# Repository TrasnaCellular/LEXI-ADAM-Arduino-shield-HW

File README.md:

# Trasna LEXI-R10 Arduino schield board

The LEXI-ADAM UNO Shield is an open-source cellular expansion board for the Arduino UNO or Arduino UNO Q platforms. It uses the ultra-small LEXI-R10 series or ADAM-R11 series LTE Cat 1bis cellular modules. 

The Cellular module can be turned ON/OFF and Reset by the Arduino board. The shield has its own step down to deliver power to the cellular module; the stepdown too can be turned ON/OFF by an Arduino GPIO to minimise power consumption. The input voltage range of the shield is the same as Arduino's range. 

The Arduino UNO  communicates with the Cellular module via UART, and by default, this communication is without RTS/CTS handshake. The shield already supports RTS/CTS handshake by easy soldering jumpers. The proper modifications must be made also to the MCU firmware of Arduino (R7FA4M1AB3CFM for UNO, or STM32U585 for UNO Q) to support hardware handshake. To achieve communication with the Linux system of Arduino UNO Q, the Arduino Bridge feature should be used. For even higher higher communication rates with the Linux system the USB port of the UNO Q must be connected to the USB port of the shield.
 
The shield also features two breadboarding areas for experimenting with own circuits. They have 2.54mm and 1.27mm pitch and are provided with 3.3Volts, 1.8Volts and GND for powering the circuits that the user might implement.

All the hardware design source files, including Schematic, PCB board, gerbers, stack-up, can be downloaded from the present repository. Also the firmware examples running on Arduino UNO R4 WIFI and on Arduino UNO Q can be found here.

The user guide explaining the board can be downloaded from: [LEXI-ADAM_Arduino_UNO_Shield_UserGuide](https://drive.google.com/file/d/1tEk1xlIRyrKd_FjjbZdSfsDOfKxhqTxc/view).

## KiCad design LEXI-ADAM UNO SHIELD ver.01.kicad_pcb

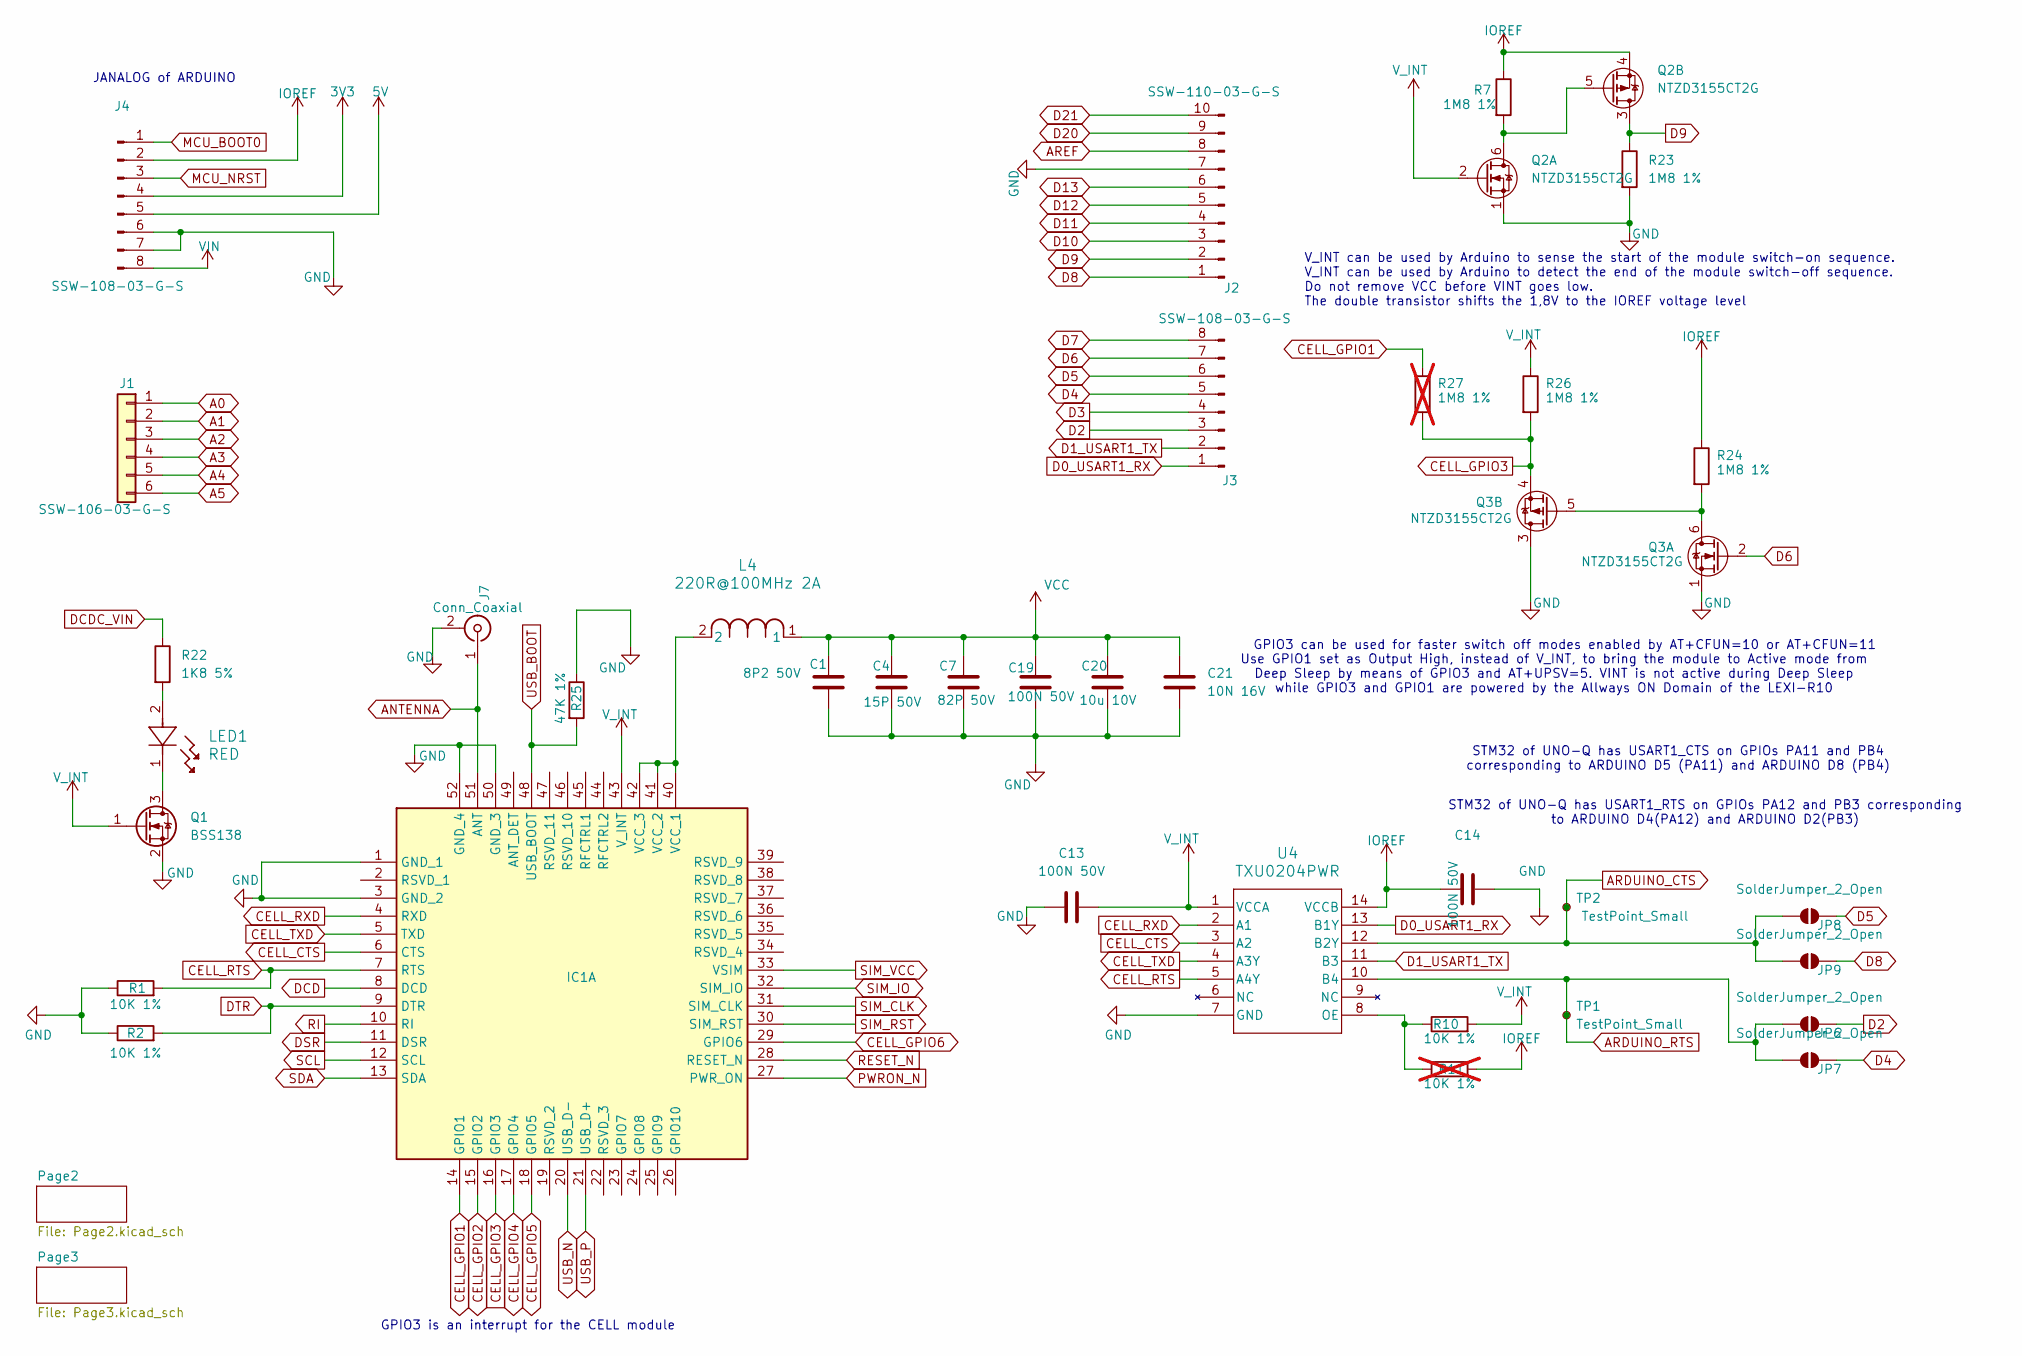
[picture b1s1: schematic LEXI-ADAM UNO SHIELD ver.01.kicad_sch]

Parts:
C1: 8P2 50V; C_0201_0603Metric; Manufacturer_Part_Number GRM0335C1H8R2DA01D
C4: 15P 50V; C_0201_0603Metric; Manufacturer_Part_Number GRM0335C1H150JA01D
C7: 82P 50V; C_0201_0603Metric; Manufacturer_Part_Number GRM0335C1H820JA01D
C13, C14, C19: 100N 50V; C_0402_1005Metric; Manufacturer_Part_Number GRM155R61H104KE14D
C20: 10u 10V; C_0402_1005Metric; Manufacturer_Part_Number GRM155R61A106ME11D
C21: 10N 16V; C_0201_0603Metric; Manufacturer_Part_Number GRM033R71C103KE14D
IC1: LEXI-R10011D; LEXIR10801D00B00; Manufacturer_Part_Number LEXI-R10011D
J1: SSW-106-03-G-S; Manufacturer_Part_Number SSW-106-03-G-S
J2: SSW-110-03-G-S; SSW-110-03-L-S; Manufacturer_Part_Number SSW-110-03-G-S
J3, J4: SSW-108-03-G-S; Manufacturer_Part_Number SSW-108-03-G-S
J7: Conn_Coaxial; U.FL_Hirose_U.FL-R-SMT-1_Vertical; Manufacturer_Part_Number CONUFL001-SMD-T
JP6, JP7, JP8, JP9: SolderJumper_2_Open; SolderJumper-2_P1.3mm_Open_RoundedPad1.0x1.5mm
L4: 220R@100MHz 2A; IND_BLM18_0603_MUR; Manufacturer_Part_Number BLM18EG221SN1D
LED1: RED; LED_LTST-C190_LTO; Manufacturer_Part_Number LTST-C190KRKT
Q1: BSS138; SOT-23; Manufacturer_Part_Number BSS138P,215
Q2, Q3: NTZD3155CT2G; SOT-563-6_1P3X1P7_ONS; Manufacturer_Part_Number NTZD3155CT2G
R1, R2, R10: 10K 1%; R_0402_1005Metric; Manufacturer_Part_Number RK73H1ETTP1002F
R7, R23, R24, R26: 1M8 1%; R_0402_1005Metric; Manufacturer_Part_Number CRCW04021M80FKEDC
R11: 10K 1%; R_0402_1005Metric; Manufacturer_Part_Number RK73H1ETTP1002F; not fitted
R22: 1K8 5%; R_0402_1005Metric; Manufacturer_Part_Number AC0402JR-071K8L
R25: 47K 1%; R_0402_1005Metric; Manufacturer_Part_Number RK73H1ETTP4702F
R27: 1M8 1%; R_0402_1005Metric; Manufacturer_Part_Number CRCW04021M80FKEDC; not fitted
TP1, TP2: TestPoint_Small; TestPoint_Pad_1.0x1.0mm
U4: TXU0204PWR; TSSOP14_PW_TEX; Manufacturer_Part_Number TXU0204PWR

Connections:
3V3: J4.4
5V: J4.5; also elsewhere on the board
A0: J1.1; also elsewhere on the board
A1: J1.2
A2: J1.3; also elsewhere on the board
A3: J1.4
A4: J1.5
A5: J1.6
ANTENNA: IC1.51 (ANT), J7.1 (In)
ARDUINO_CTS: JP8.1 (A), JP9.1 (A), TP2.1, U4.12 (B2Y)
ARDUINO_RTS: JP6.1 (A), JP7.1 (A), TP1.1, U4.10 (B4)
AREF: J2.8
CELL_CTS: IC1.6 (CTS), U4.3 (A2)
CELL_GPIO1: IC1.14 (GPIO1), R27.1; also elsewhere on the board
CELL_GPIO2: IC1.15 (GPIO2); also elsewhere on the board
CELL_GPIO3: IC1.16 (GPIO3), Q3.4 (SP), R26.2, R27.2
CELL_GPIO4: IC1.17 (GPIO4); also elsewhere on the board
CELL_GPIO5: IC1.18 (GPIO5); also elsewhere on the board
CELL_GPIO6: IC1.29 (GPIO6); also elsewhere on the board
CELL_RTS: IC1.7 (RTS), R1.2, U4.5 (A4Y)
CELL_RXD: IC1.4 (RXD), U4.2 (A1)
CELL_TXD: IC1.5 (TXD), U4.4 (A3Y)
D0_USART1_RX: J3.1, U4.13 (B1Y)
D1_USART1_TX: J3.2, U4.11 (B3)
D2: J3.3, JP6.2 (B)
D3: J3.4; also elsewhere on the board
D4: J3.5, JP7.2 (B)
D5: J3.6, JP8.2 (B)
D6: J3.7, Q3.2 (GN)
D7: J3.8; also elsewhere on the board
D8: J2.1, JP9.2 (B)
D9: J2.2, Q2.3 (DP), R23.1
D10: J2.3
D11: J2.4
D12: J2.5
D13: J2.6
D20: J2.9
D21: J2.10
DCD: IC1.8 (DCD)
DCDC_VIN: R22.1; also elsewhere on the board
DSR: IC1.11 (DSR)
DTR: IC1.9 (DTR), R2.2
GND: C1.1, C4.2, C7.2, C13.2, C14.1, C19.2, C20.2, C21.2, IC1.1 (GND_1), IC1.3 (GND_2), IC1.50 (GND_3), IC1.52 (GND_4), J2.7, J4.6, J4.7, J7.2 (Ext), Q1.2 (S), Q2.1 (SN), Q3.1 (SN), Q3.3 (DP), R1.1, R2.1, R23.2, R25.1, U4.7 (GND); also elsewhere on the board
IOREF: C14.2, J4.2, Q2.4 (SP), R7.1, R11.2, R24.1, U4.14 (VCCB); also elsewhere on the board
MCU_BOOT0: J4.1
MCU_NRST: J4.3
unnamed: IC1.40 (VCC_1), IC1.41 (VCC_2), IC1.42 (VCC_3), L4.2
unnamed: LED1.2, R22.2
unnamed: LED1.1, Q1.3 (D)
unnamed: Q2.5 (GP), Q2.6 (DN), R7.2
unnamed: Q3.5 (GP), Q3.6 (DN), R24.2
unnamed: R10.1, R11.1, U4.8 (OE)
PWRON_N: IC1.27 (PWR_ON); also elsewhere on the board
RESET_N: IC1.28 (RESET_N); also elsewhere on the board
RI: IC1.10 (RI); also elsewhere on the board
SCL: IC1.12 (SCL); also elsewhere on the board
SDA: IC1.13 (SDA); also elsewhere on the board
SIM_CLK: IC1.31 (SIM_CLK); also elsewhere on the board
SIM_IO: IC1.32 (SIM_IO); also elsewhere on the board
SIM_RST: IC1.30 (SIM_RST); also elsewhere on the board
SIM_VCC: IC1.33 (VSIM); also elsewhere on the board
USB_BOOT: IC1.48 (USB_BOOT), R25.2; also elsewhere on the board
USB_N: IC1.20 (USB_D-); also elsewhere on the board
USB_P: IC1.21 (USB_D+); also elsewhere on the board
VCC: C1.2, C4.1, C7.1, C19.1, C20.1, C21.1, L4.1; also elsewhere on the board
VIN: J4.8; also elsewhere on the board
V_INT: C13.1, IC1.43 (V_INT), Q1.1 (G), Q2.2 (GN), R10.2, R26.1, U4.1 (VCCA); also elsewhere on the board

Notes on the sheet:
V_INT can be used by Arduino to sense the start of the module switch-on sequence. V_INT can be used by Arduino to detect the end of the module switch-off sequence. Do not remove VCC before VINT goes low. The double transistor shifts the 1,8V to the IOREF voltage level
Use GPIO1 set as Output High, instead of V_INT, to bring the module to Active mode from Deep Sleep by means of GPIO3 and AT+UPSV=5. VINT is not active during Deep Sleep while GPIO3 and GPIO1 are powered by the Allways ON Domain of the LEXI-R10
JANALOG of ARDUINO
GPIO3 can be used for faster switch off modes enabled by AT+CFUN=10 or AT+CFUN=11
STM32 of UNO-Q has USART1_CTS on GPIOs PA11 and PB4 corresponding to ARDUINO D5 (PA11) and ARDUINO D8 (PB4)
STM32 of UNO-Q has USART1_RTS on GPIOs PA12 and PB3 corresponding to ARDUINO D4(PA12) and ARDUINO D2(PB3)
GPIO3 is an interrupt for the CELL module

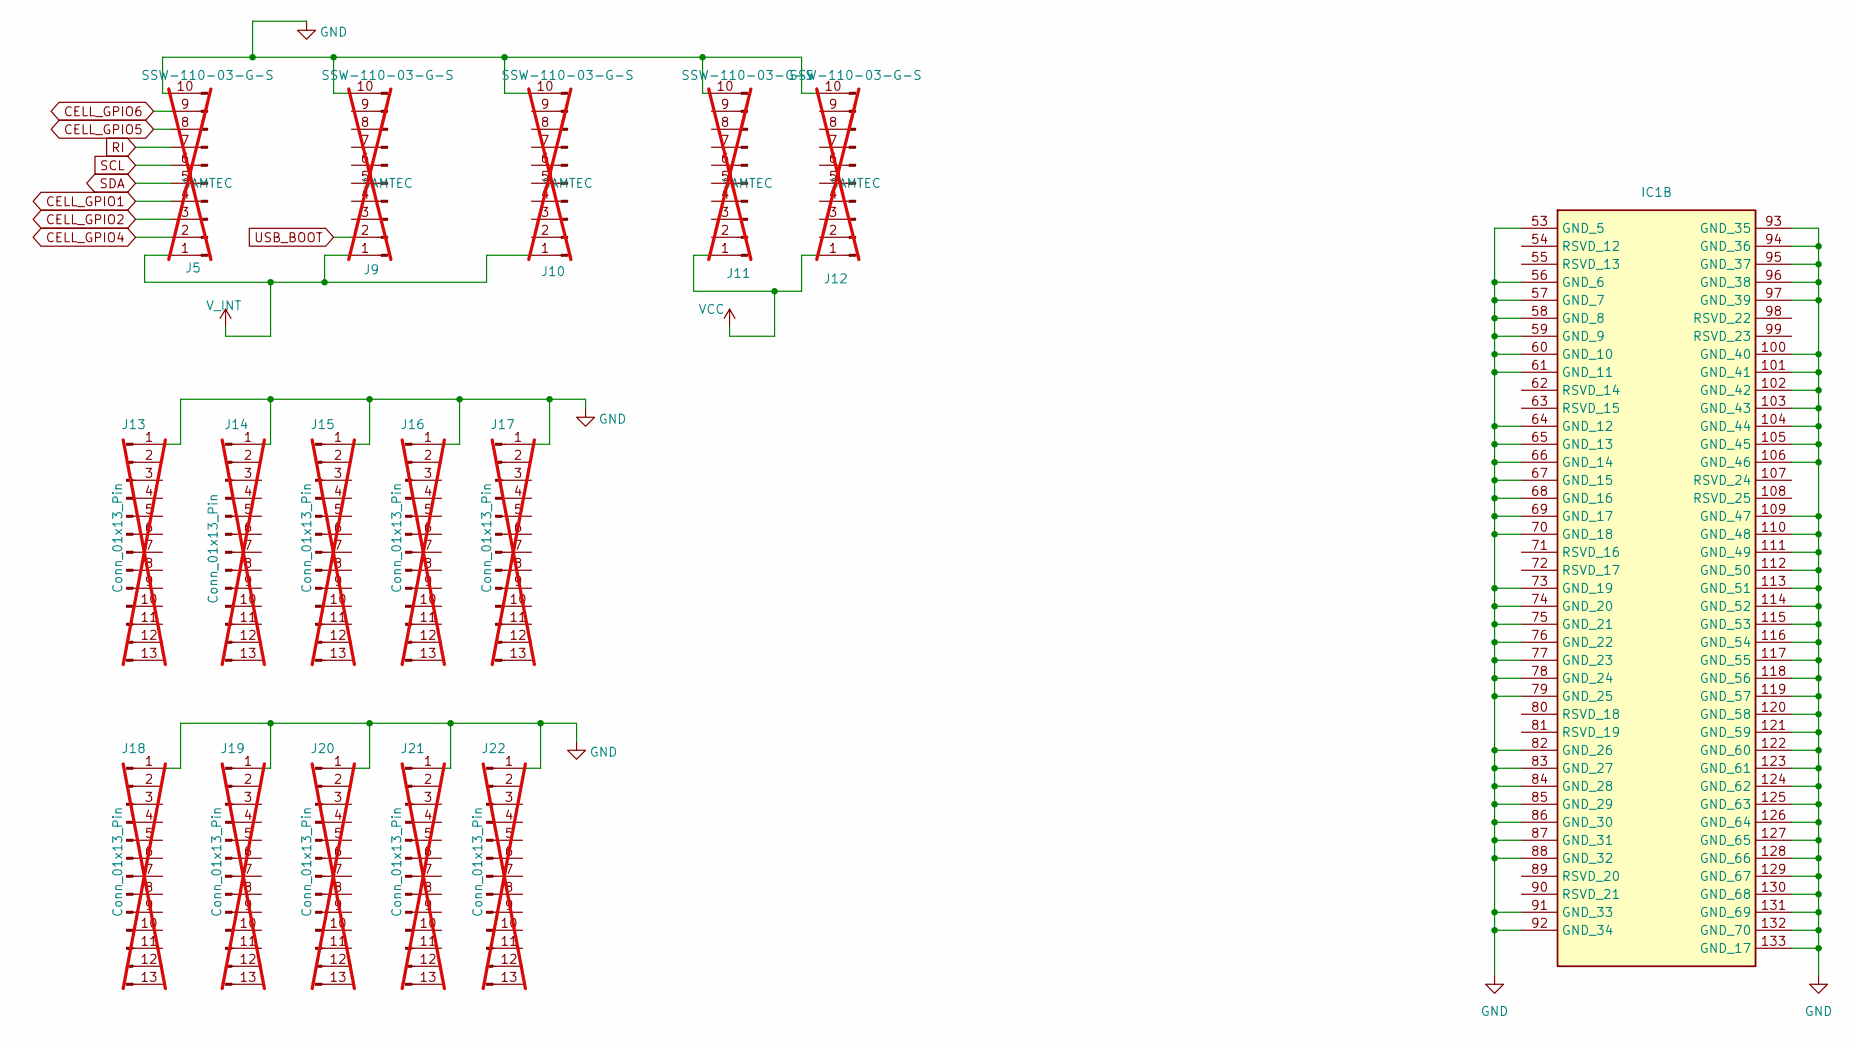
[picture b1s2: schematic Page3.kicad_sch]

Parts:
IC1: LEXI-R10011D; LEXIR10801D00B00; Manufacturer_Part_Number LEXI-R10011D
J5, J9, J10, J11, J12: SSW-110-03-G-S; SSW-110-03-L-S; Manufacturer_Part_Number SSW-110-03-G-S; not fitted
J13, J14, J15, J16, J17, J18, J19, J20, J21, J22: Conn_01x13_Pin; PinHeader_1x13_P1.27mm_Vertical_minimum_courtyard; not fitted

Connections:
CELL_GPIO1: J5.4; also elsewhere on the board
CELL_GPIO2: J5.3; also elsewhere on the board
CELL_GPIO4: J5.2; also elsewhere on the board
CELL_GPIO5: J5.8; also elsewhere on the board
CELL_GPIO6: J5.9; also elsewhere on the board
GND: IC1.53 (GND_5), IC1.56 (GND_6), IC1.57 (GND_7), IC1.58 (GND_8), IC1.59 (GND_9), IC1.60 (GND_10), IC1.61 (GND_11), IC1.64 (GND_12), IC1.65 (GND_13), IC1.66 (GND_14), IC1.67 (GND_15), IC1.68 (GND_16), IC1.69 (GND_17), IC1.70 (GND_18), IC1.73 (GND_19), IC1.74 (GND_20), IC1.75 (GND_21), IC1.76 (GND_22), IC1.77 (GND_23), IC1.78 (GND_24), IC1.79 (GND_25), IC1.82 (GND_26), IC1.83 (GND_27), IC1.84 (GND_28), IC1.85 (GND_29), IC1.86 (GND_30), IC1.87 (GND_31), IC1.88 (GND_32), IC1.91 (GND_33), IC1.92 (GND_34), IC1.93 (GND_35), IC1.94 (GND_36), IC1.95 (GND_37), IC1.96 (GND_38), IC1.97 (GND_39), IC1.100 (GND_40), IC1.101 (GND_41), IC1.102 (GND_42), IC1.103 (GND_43), IC1.104 (GND_44), IC1.105 (GND_45), IC1.106 (GND_46), IC1.109 (GND_47), IC1.110 (GND_48), IC1.111 (GND_49), IC1.112 (GND_50), IC1.113 (GND_51), IC1.114 (GND_52), IC1.115 (GND_53), IC1.116 (GND_54), IC1.117 (GND_55), IC1.118 (GND_56), IC1.119 (GND_57), IC1.120 (GND_58), IC1.121 (GND_59), IC1.122 (GND_60), IC1.123 (GND_61), IC1.124 (GND_62), IC1.125 (GND_63), IC1.126 (GND_64), IC1.127 (GND_65), IC1.128 (GND_66), IC1.129 (GND_67), IC1.130 (GND_68), IC1.131 (GND_69), IC1.132 (GND_70), IC1.133 (GND_17), J5.10, J9.10, J10.10, J11.10, J12.10, J13.1, J14.1, J15.1, J16.1, J17.1, J18.1, J19.1, J20.1, J21.1, J22.1; also elsewhere on the board
RI: J5.7; also elsewhere on the board
SCL: J5.6; also elsewhere on the board
SDA: J5.5; also elsewhere on the board
USB_BOOT: J9.2; also elsewhere on the board
VCC: J11.1, J12.1; also elsewhere on the board
V_INT: J5.1, J9.1, J10.1; also elsewhere on the board

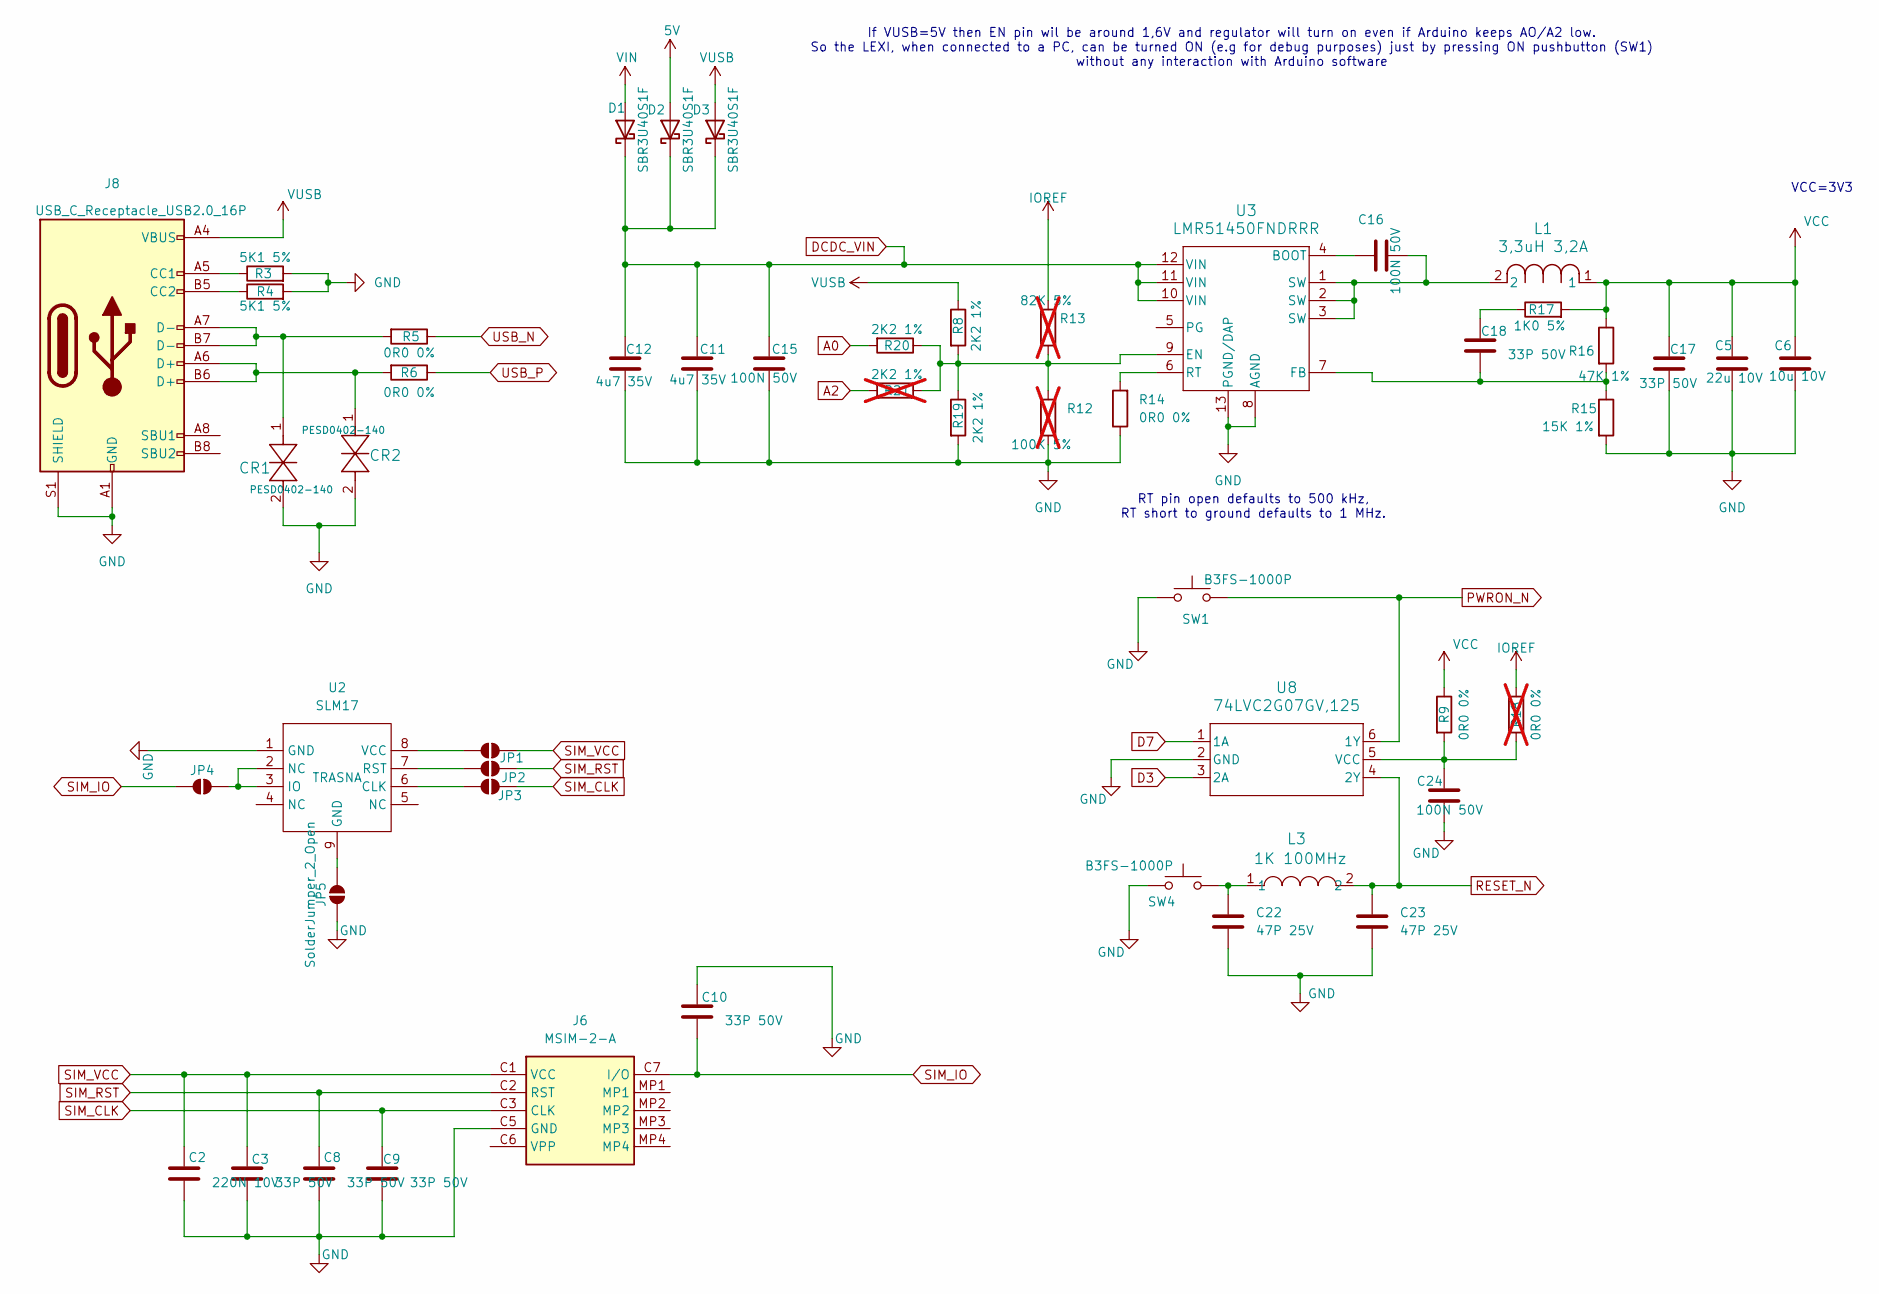
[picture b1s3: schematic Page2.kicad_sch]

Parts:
C2: 220N 10V; C_0201_0603Metric; Manufacturer_Part_Number GRM033R61A224ME90D
C3, C8, C9, C10, C17, C18: 33P 50V; C_0201_0603Metric; Manufacturer_Part_Number GRM0335C1H330JA01D
C5: 22u 10V; C_0603_1608Metric; Manufacturer_Part_Number GRM188R61A226ME15D
C6: 10u 10V; C_0402_1005Metric; Manufacturer_Part_Number GRM155R61A106ME11D
C11, C12: 4u7 35V; C_0805_2012Metric; Manufacturer_Part_Number GRM21BZ7YA475KE15K
C15, C16, C24: 100N 50V; C_0402_1005Metric; Manufacturer_Part_Number GRM155R61H104KE14D
C22, C23: 47P 25V; C_0201_0603Metric; Manufacturer_Part_Number GRM0335C1H470JA01D
CR1, CR2: PESD0402-140; PESD0402-140_LTF; Manufacturer_Part_Number PESD0402-140
D1, D2, D3: SBR3U40S1F; D_SOD-123F; Manufacturer_Part_Number SBR3U40S1FQ-7
J6: MSIM-2-A; MSIM2A; Mouser Part Number 179-MSIM-2-A
J8: USB_C_Receptacle_USB2.0_16P; USB_C_Receptacle_GCT_USB4105-xx-A_16P_TopMnt_Horizontal; Manufacturer_Part_Number 12402012E212A
JP1, JP2, JP3, JP4, JP5: SolderJumper_2_Open; SolderJumper-2_P1.3mm_Open_RoundedPad1.0x1.5mm
L1: 3,3uH 3,2A; IND_IFSC-2020DE-01_VIS; Manufacturer_Part_Number IFSC2020DEER3R3N01
L3: 1K 100MHz; IND_BLM15_0402_MUR; Manufacturer_Part_Number BLM15HD102SN1D
R3, R4: 5K1 5%; R_0402_1005Metric; Manufacturer_Part_Number RK73B1ETTP512J
R5, R6, R9, R14: 0R0 0%; R_0402_1005Metric; Manufacturer_Part_Number RC0402JR-070RL
R8, R19, R20: 2K2 1%; R_0402_1005Metric; Manufacturer_Part_Number RK73H1ETTP2201F
R12: 100K 5%; R_0402_1005Metric; Manufacturer_Part_Number RC0402JR-07100KL; not fitted
R13: 82K 5%; R_0402_1005Metric; Manufacturer_Part_Number MCR01MZPJ823; not fitted
R15: 15K 1%; R_0402_1005Metric; Manufacturer_Part_Number RK73H1ETTP1502F
R16: 47K 1%; R_0402_1005Metric; Manufacturer_Part_Number RK73H1ETTP4702F
R17: 1K0 5%; R_0402_1005Metric; Manufacturer_Part_Number RK73B1ETTP102J
R18: 0R0 0%; R_0402_1005Metric; Manufacturer_Part_Number RC0402JR-070RL; not fitted
R21: 2K2 1%; R_0402_1005Metric; Manufacturer_Part_Number RK73H1ETTP2201F; not fitted
SW1, SW4: B3FS-1000P; SW_SPST_Omron_B3FS-100xP; Manufacturer_Part_Number B3FS-1000P
U2: SLM17; Infineon_USON_2x2mm_P0.5mm_EP0.9x1.6mm
U3: LMR51450FNDRRR; WSON12-DRR_TEX; Manufacturer_Part_Number LMR51450FNDRRR
U8: 74LVC2G07GV,125; 74LVC2G07GV_125_NEX; Manufacturer_Part_Number 74LVC2G07GV,125

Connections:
5V: D2.2 (A); also elsewhere on the board
A0: R20.2; also elsewhere on the board
A2: R21.2; also elsewhere on the board
D3: U8.3 (2A); also elsewhere on the board
D7: U8.1 (1A); also elsewhere on the board
DCDC_VIN: C11.1, C12.1, C15.1, D1.1 (K), D2.1 (K), D3.1 (K), U3.10 (VIN), U3.11 (VIN), U3.12 (VIN); also elsewhere on the board
GND: C2.2, C3.2, C5.2, C6.2, C8.2, C9.2, C10.1, C11.2, C12.2, C15.2, C17.2, C22.2, C23.2, C24.2, CR1.2, CR2.2, J6.C5 (GND), J8.A1 (GND), J8.A12 (GND), J8.B1 (GND), J8.B12 (GND), J8.S1 (SHIELD), JP5.1 (A), R3.2, R4.2, R12.2, R14.1, R15.2, R19.2, SW1.1, SW4.1, U2.1 (GND), U3.8 (AGND), U3.13 (PGND/DAP), U8.2 (GND); also elsewhere on the board
IOREF: R13.1, R18.1; also elsewhere on the board
unnamed: C16.2, L1.2, U3.1 (SW), U3.2 (SW), U3.3 (SW)
unnamed: C18.1, R17.1
unnamed: C22.1, L3.1, SW4.2
unnamed: CR1.1, J8.A7 (D-), J8.B7 (D-), R5.2
unnamed: CR2.1, J8.A6 (D+), J8.B6 (D+), R6.2
unnamed: J8.A5 (CC1), R3.1
unnamed: J8.B5 (CC2), R4.1
unnamed: JP1.1 (A), U2.8 (VCC)
unnamed: JP2.1 (A), U2.7 (RST)
unnamed: JP3.1 (A), U2.6 (CLK)
unnamed: JP4.2 (B), U2.2 (NC), U2.3 (IO)
unnamed: JP5.2 (B), U2.9 (GND)
unnamed: C16.1, U3.4 (BOOT)
unnamed: R8.2, R12.1, R13.2, R19.1, R20.1, R21.1, U3.9 (EN)
unnamed: C18.2, R15.1, R16.2, U3.7 (FB)
unnamed: R14.2, U3.6 (RT)
unnamed: C24.1, R9.2, R18.2, U8.5 (VCC)
PWRON_N: SW1.2, U8.6 (1Y); also elsewhere on the board
RESET_N: C23.1, L3.2, U8.4 (2Y); also elsewhere on the board
SIM_CLK: C9.1, J6.C3 (CLK), JP3.2 (B); also elsewhere on the board
SIM_IO: C10.2, J6.C7 (I/O), JP4.1 (A); also elsewhere on the board
SIM_RST: C8.1, J6.C2 (RST), JP2.2 (B); also elsewhere on the board
SIM_VCC: C2.1, C3.1, J6.C1 (VCC), JP1.2 (B); also elsewhere on the board
USB_N: R5.1; also elsewhere on the board
USB_P: R6.1; also elsewhere on the board
VCC: C5.1, C6.1, C17.1, L1.1, R9.1, R16.1, R17.2; also elsewhere on the board
VIN: D1.2 (A); also elsewhere on the board
VUSB: D3.2 (A), J8.A4 (VBUS), J8.A9 (VBUS), J8.B4 (VBUS), J8.B9 (VBUS), R8.1

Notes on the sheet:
RT pin open defaults to 500 kHz, RT short to ground defaults to 1 MHz.
If VUSB=5V then EN pin wil be around 1,6V and regulator will turn on even if Arduino keeps AO/A2 low. So the LEXI, when connected to a PC, can be turned ON (e.g for debug purposes) just by pressing ON pushbutton (SW1) without any interaction with Arduino software
VCC=3V3

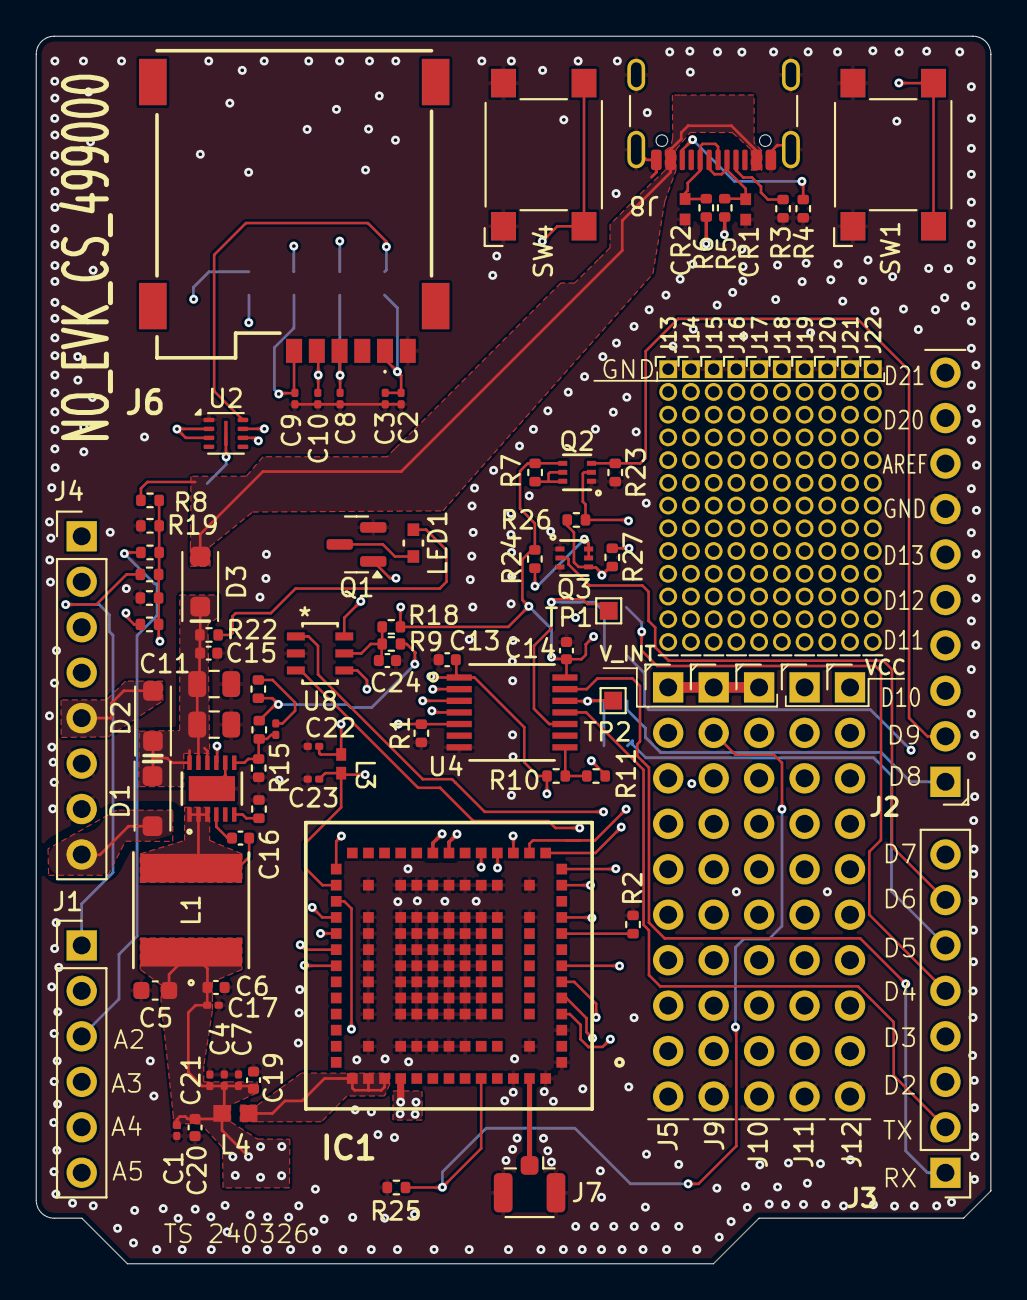
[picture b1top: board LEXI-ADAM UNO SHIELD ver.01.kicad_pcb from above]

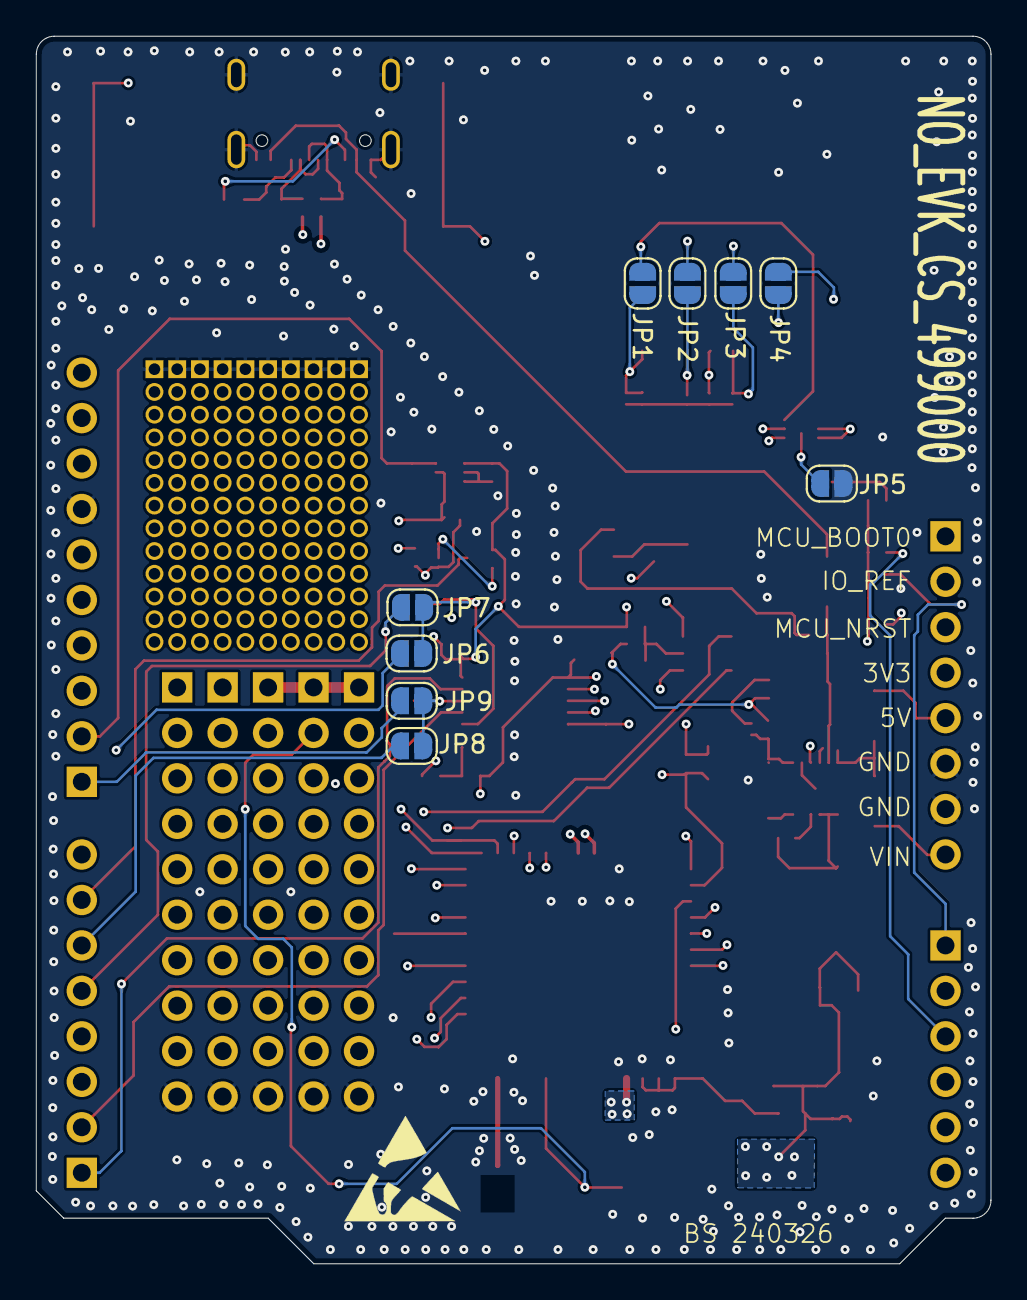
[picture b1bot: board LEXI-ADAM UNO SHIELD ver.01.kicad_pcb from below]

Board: 4 copper layers, 53.3 x 68.6 mm, 103 parts (9 on the bottom side), 69 nets.

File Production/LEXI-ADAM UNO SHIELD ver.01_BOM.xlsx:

### Footprint positions - created on 2026-03-24T11:52:16+0100 ### ### Printed b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
Ref | Val | Package | PosX | PosY | Rot | Side
C1 | 8P2_50V | C_0201_0603Metric | 7.8520 | 7.4630 | 90.0000 | top
C2 | 220N_10V | C_0201_0603Metric | 20.3880 | 48.3400 | -90.0000 | top
C3 | 33P_50V | C_0201_0603Metric | 19.5000 | 48.3400 | -90.0000 | top
C4 | 15P_50V | C_0201_0603Metric | 10.5073 | 10.2558 | 90.0000 | top
C5 | 22u_10V | C_0603_1608Metric | 6.6480 | 15.2680 | 180.0000 | top
C6 | 10u_10V | C_0402_1005Metric | 10.0440 | 15.4390 | 0.0000 | top
C7 | 82P_50V | C_0201_0603Metric | 11.3013 | 10.2558 | 90.0000 | top
C8 | 33P_50V | C_0201_0603Metric | 16.9780 | 48.3400 | -90.0000 | top
C9 | 33P_50V | C_0201_0603Metric | 14.4520 | 48.3400 | -90.0000 | top
C10 | 33P_50V | C_0201_0603Metric | 15.7320 | 48.3400 | 90.0000 | top
C11 | 4u7_35V | C_0805_2012Metric | 9.9433 | 32.3908 | 0.0000 | top
C12 | 4u7_35V | C_0805_2012Metric | 9.9433 | 30.1248 | 0.0000 | top
C13 | 100N_50V | C_0402_1005Metric | 22.9640 | 33.7510 | 180.0000 | top
C14 | 100N_50V | C_0402_1005Metric | 29.6260 | 34.2580 | -90.0000 | top
C15 | 100N_50V | C_0402_1005Metric | 9.6340 | 34.1180 | 0.0000 | top
C16 | 100N_50V | C_0402_1005Metric | 11.4150 | 23.7830 | 0.0000 | top
C17 | 33P_50V | C_0201_0603Metric | 9.8730 | 14.4440 | 0.0000 | top
C18 | 33P_50V | C_0201_0603Metric | 13.3840 | 29.8700 | -90.0000 | top
C19 | 100N_50V | C_0402_1005Metric | 12.1393 | 10.2558 | 90.0000 | top
C20 | 10u_10V | C_0402_1005Metric | 8.8733 | 7.6118 | -90.0000 | top
C21 | 10N_16V | C_0201_0603Metric | 9.7003 | 10.2508 | 90.0000 | top
C22 | 47P_25V | C_0201_0603Metric | 15.4900 | 28.9080 | 180.0000 | top
C23 | 47P_25V | C_0201_0603Metric | 15.4900 | 27.0770 | 180.0000 | top
C24 | 100N_50V | C_0402_1005Metric | 19.6220 | 33.7040 | 0.0000 | top
CR1 | PESD0402-140 | PESD0402-140_LTF | 39.6400 | 58.9100 | -90.0000 | top
CR2 | PESD0402-140 | PESD0402-140_LTF | 36.2540 | 58.9210 | -90.0000 | top
D1 | SBR3U40S1F | D_SOD-123F | 6.4963 | 25.8493 | -90.0000 | top
D2 | SBR3U40S1F | D_SOD-123F | 6.5233 | 30.6048 | 90.0000 | top
D3 | SBR3U40S1F | D_SOD-123F | 9.1620 | 38.1180 | 90.0000 | top
IC1 | LEXI-R10011D | LEXIR10801D00B00 | 23.0610 | 16.6510 | 180.0000 | top
J1 | SSW-106-03-G-S | SSW-106-03-G-S | 2.5400 | 17.7856 | 0.0000 | top
J2 | SSW-110-03-G-S | SSW-110-03-L-S | 50.8000 | 26.9300 | 180.0000 | top
J3 | SSW-108-03-G-S | SSW-108-03-G-S | 50.8000 | 5.0856 | 180.0000 | top
J4 | SSW-108-03-G-S | SSW-108-03-G-S | 2.5400 | 40.6456 | 0.0000 | top
J5 | SSW-110-03-G-S | SSW-110-03-L-S | 35.3100 | 32.2020 | 0.0000 | top
J6 | MSIM-2-A | MSIM2A | 14.4170 | 59.1966 | 180.0000 | top
J7 | Conn_Coaxial | U.FL_Hirose_U.FL-R-SMT-1_Vertical | 27.5650 | 4.4430 | -90.0000 | top
J8 | USB_C_Receptacle_USB2.0_16P | USB_C_Receptacle_GCT_USB4105-xx-A_16P_TopMnt_Horizontal | 37.8460 | 65.3572 | 180.0000 | top
J9 | SSW-110-03-G-S | SSW-110-03-L-S | 37.8500 | 32.2020 | 0.0000 | top
J10 | SSW-110-03-G-S | SSW-110-03-L-S | 40.3900 | 32.2020 | 0.0000 | top
J11 | SSW-110-03-G-S | SSW-110-03-L-S | 42.9300 | 32.2020 | 0.0000 | top
J12 | SSW-110-03-G-S | SSW-110-03-L-S | 45.4700 | 32.2020 | 0.0000 | top
J13 | Conn_01x13_Pin | PinHeader_1x13_P1.27mm_Vertical_minimum_courtyard | 35.3100 | 49.9820 | 0.0000 | top
J14 | Conn_01x13_Pin | PinHeader_1x13_P1.27mm_Vertical_minimum_courtyard | 36.5800 | 49.9820 | 0.0000 | top
J15 | Conn_01x13_Pin | PinHeader_1x13_P1.27mm_Vertical_minimum_courtyard | 37.8500 | 49.9820 | 0.0000 | top
J16 | Conn_01x13_Pin | PinHeader_1x13_P1.27mm_Vertical_minimum_courtyard | 39.1200 | 49.9820 | 0.0000 | top
J17 | Conn_01x13_Pin | PinHeader_1x13_P1.27mm_Vertical_minimum_courtyard | 40.3900 | 49.9820 | 0.0000 | top
J18 | Conn_01x13_Pin | PinHeader_1x13_P1.27mm_Vertical_minimum_courtyard | 41.6600 | 49.9820 | 0.0000 | top
J19 | Conn_01x13_Pin | PinHeader_1x13_P1.27mm_Vertical_minimum_courtyard | 42.9300 | 49.9820 | 0.0000 | top
J20 | Conn_01x13_Pin | PinHeader_1x13_P1.27mm_Vertical_minimum_courtyard | 44.2000 | 49.9820 | 0.0000 | top
J21 | Conn_01x13_Pin | PinHeader_1x13_P1.27mm_Vertical_minimum_courtyard | 45.4700 | 49.9820 | 0.0000 | top
J22 | Conn_01x13_Pin | PinHeader_1x13_P1.27mm_Vertical_minimum_courtyard | 46.7400 | 49.9820 | 0.0000 | top
L1 | 3,3uH_3,2A | IND_IFSC-2020DE-01_VIS | 8.6543 | 19.7538 | 90.0000 | top
L3 | 1K_100MHz | IND_BLM15_0402_MUR | 17.0380 | 27.9320 | -90.0000 | top
L4 | 220R@100MHz_2A | IND_BLM18_0603_MUR | 11.1293 | 8.4008 | 0.0000 | top
LED1 | RED | LED_LTST-C190_LTO | 21.0702 | 40.2670 | 90.0000 | top
Q1 | BSS138 | SOT-23 | 17.8942 | 40.1920 | 180.0000 | top
Q2 | NTZD3155CT2G | SOT-563-6_1P3X1P7_ONS | 30.2190 | 44.2210 | 180.0000 | top
Q3 | NTZD3155CT2G | SOT-563-6_1P3X1P7_ONS | 30.0630 | 39.4350 | 0.0000 | top
R1 | 10K_1% | R_0402_1005Metric | 21.5160 | 29.6400 | 90.0000 | top
R2 | 10K_1% | R_0402_1005Metric | 33.3460 | 18.9540 | -90.0000 | top
R3 | 5K1_5% | R_0402_1005Metric | 41.7280 | 58.9520 | -90.0000 | top
R4 | 5K1_5% | R_0402_1005Metric | 42.8540 | 58.9520 | -90.0000 | top
R5 | 0R0_0% | R_0402_1005Metric | 38.4680 | 58.9970 | 90.0000 | top
R6 | 0R0_0% | R_0402_1005Metric | 37.4370 | 58.9970 | 90.0000 | top
R7 | 1M8_1% | R_0402_1005Metric | 27.8710 | 44.2100 | -90.0000 | top
R8 | 47K_1% | R_0402_1005Metric | 6.3580 | 42.6530 | 0.0000 | top
R9 | 0R0_0% | R_0402_1005Metric | 19.8410 | 34.6300 | 180.0000 | top
R10 | 10K_1% | R_0402_1005Metric | 29.0501 | 27.2530 | 180.0000 | top
R11 | 10K_1% | R_0402_1005Metric | 31.2760 | 27.2530 | 0.0000 | top
R12 | 100K_5% | R_0402_1005Metric | 6.3290 | 37.1990 | 180.0000 | top
R13 | 82K_5% | R_0402_1005Metric | 6.3290 | 35.7240 | 0.0000 | top
R14 | 0R0_0% | R_0402_1005Metric | 12.4440 | 25.4020 | -90.0000 | top
R15 | 15K_1% | R_0402_1005Metric | 12.4290 | 27.6950 | -90.0000 | top
R16 | 47K_1% | R_0402_1005Metric | 12.4580 | 29.8340 | -90.0000 | top
R17 | 1K0_5% | R_0402_1005Metric | 12.4080 | 32.1090 | -90.0000 | top
R18 | 0R0_0% | R_0402_1005Metric | 19.8390 | 35.5840 | 180.0000 | top
R19 | 47K_1% | R_0402_1005Metric | 6.3580 | 41.2300 | 180.0000 | top
R20 | 47K_1% | R_0402_1005Metric | 6.3290 | 38.5140 | 180.0000 | top
R21 | 47K_1% | R_0402_1005Metric | 6.3580 | 39.7420 | 180.0000 | top
R22 | 1K8_5% | R_0402_1005Metric | 9.6540 | 35.1340 | 0.0000 | top
R23 | 1M8_1% | R_0402_1005Metric | 32.3500 | 44.2100 | -90.0000 | top
R24 | 1M8_1% | R_0402_1005Metric | 27.8590 | 39.3750 | -90.0000 | top
R25 | 47K_1% | R_0402_1005Metric | 20.1220 | 4.2600 | 0.0000 | top
R26 | 1M8_1% | R_0402_1005Metric | 30.1790 | 41.5600 | 180.0000 | top
R27 | 1M8_1% | R_0402_1005Metric | 32.1840 | 39.4670 | -90.0000 | top
SW1 | B3FS-1000P | SW_SPST_Omron_B3FS-100xP | 47.8810 | 61.9660 | 90.0000 | top
SW4 | B3FS-1000P | SW_SPST_Omron_B3FS-100xP | 28.3560 | 61.9660 | 90.0000 | top
U2 | SLM17 | Infineon_USON_2x2mm_P0.5mm_EP0.9x1.6mm | 10.5985 | 46.3965 | 0.0000 | top
U3 | LMR51450FNDRRR | WSON12-DRR_TEX | 9.8133 | 26.5488 | 90.0000 | top
U4 | TXU0204PWR | TSSOP14_PW_TEX | 26.5861 | 30.8050 | 0.0000 | top
U8 | 74LVC2G07GV,125 | 74LVC2G07GV_125_NEX | 15.8590 | 34.1000 | 0.0000 | top

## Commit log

2026-01-27 test1
2026-05-26 Content release
2026-06-03 Add user guide document link
